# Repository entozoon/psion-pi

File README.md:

# Psion Pi

Personal electronics project; Attempting to build a modern PDA clamshell computer in a likeness of the venerable Psion 5mx.

4 years into this project, some significant changes, namely wide screen, LG Phenom keyboard and Pi 4 (significantly more capable.. the previous Zero/Zero 2/3 all put me off)

<!---KANBAN
# To Do
- Battery build protected/stepped-up/hooked up
- Battery level (physical or reported to Pi, ie. via lipo fuel gauge)
- Case build
- Keyboard scanning/emulation
- Wireless charging if possible

# In Progress
- Power converters

# Done
- Bootable Pi
- LCD screen
- Touch screen
- Figure power requirements
KANBAN--->

## Aims

- Tasty colour screen - For enjoyable video playback
- Quality keyboard - So it's legitimately useful
- Portability - I'm under no illusions that it'll be larger than a Psion 5mx/Jornada (as would be ideal) because of screen size and battery demands but if it's smaller than a Netbook Pro I'll be happy
- Sturdiness - Every single bit will be inherently fragile as heck, so I need to 3D print the structure real good

## Ingredients

- Battery pack (18650 3S parallel 3.7v) - Home-made li-ion for the win!
- Charging circuity and steps ups with protection - So I don't blow myself up
- Raspberry Pi
- LG Phenom keyboard, or maybe Psion Netbook (previously Psion 5mx, prepreviously Dell Foldable) - What? No way! Yes way. **Yes frickin way**
- Keyboard USB interface - Arduino or ESP8266, hand-built
- 7.9" Capacitive Touchscreen LCD 1024\*600 (Waveshare C Rev2.1)
- Mad efficient 1337 OS and warez, legit IDE, etc - We'll start with vanilla Raspbian first though

## "Wait, so what's this repo even for then?"

Notes about how I set everything up for reference, config files, microcontroller code for keyboard interface, etc etc.

## Setting up the Pi

Raspbian Stretch (2017-08-16) did **not** work, no matter what (with Pi Zeroes).

Raspbian Jessie (2017-07-05) did though, but more recently..

Raspberry Pi OS Bullseye [(2021-11-08)](https://downloads.raspberrypi.org/raspios_lite_arm64/images/) is 64-bit(!)

Installed on a 16gb microSD with win32diskImager (or similar) then, _before removing_, (in the windows partition, or `/boot` on unix):

1. Create a blank file called `ssh` on it, e.g.

```bash
cd /d h:
echo > ssh
```

2. Create `wpa_supplicant.conf` containing:

```bash
country=US
ctrl_interface=DIR=/var/run/wpa_supplicant GROUP=netdev
update_config=1

network={
 ssid="NetworkName"
 scan_ssid=1
 psk="yourpassword"
 key_mgmt=WPA-PSK
}
```

3. Safely eject (they can become corrupt, trust)
4. Pop it in the Pi with HDMI and a keyboard; let it do its thing.

Any screen problems and it should still be SSH-able.

## LCD Screen - 7.9" Waveshare Widescreen 400×1280

### Enable HDMI current and whatnot

```bash
sudo nano /boot/config.txt
```

```bash
# Add support for 7.9" Waveshare LCD
# set current over USB to 1.2A
max_usb_current=1
hdmi_group=2
hdmi_mode=87
hdmi_timings=400 0 100 10 140 1280 10 20 20 2 0 0 0 60 0 43000000 3
# 1: 90°; 2: 180°C; 3: 270° (might not work, see next section)
#lcd_rotate=3
#hdmi_enable_4kp60=1
```

### Disable compositor

```bash
sudo raspi-config
```

6 Advanced menu then A3 and set Compositor to disabled.

### Rotate

Set orientation (right) in raspbian `preferences > screen configuration`.
This appears to have a bug where the settings don't persist after boot - it creates a file called dispsetup.sh but doesn't appear to run after login, at least on my current distro, so let's force it:

```bash
sudo nano /etc/xdg/lxsession/LXDE-pi/autostart
```

Append:

```
@/usr/share/dispsetup.sh
```

## Touch Setup

Automatic and orientated by long-pressing the 'rotate touch' button on the screen.

## Brightness

Powers happily from the touch USB input!!

Has 5 Settings, long press on/off on screen:

- 1 0.15A
- 2 0.16A
- 3 0.17A
- 4 0.19A
- 5 0.2A

## Fan Shim

```bash
git clone https://github.com/pimoroni/fanshim-python
cd fanshim-python
sudo ./install.sh
cd examples
sudo ./install-service.sh --on-threshold 65 --off-threshold 55 --delay 2
```

## Overclock

Make sure to use the fan shim!

```bash
sudo nano /boot/config.txt
```

```
# Overclock (all values typically unset, defaulting to 700mhz)
over_voltage=4
arm_freq=2000
```

More steps involved.. https://www.tomshardware.com/how-to/raspberry-pi-4-23-ghz-overclock

## Other settings

Disable dimming, etc.. https://www.waveshare.com/wiki/7.9inch_HDMI_LCD

## Power Usage

|                 Component | Usage (Amps +/- 0.05) |
| ------------------------: | --------------------- |
|                 Pi Zero W | 0.15 (unused)         |
|                      Pi 3 | 0.3 (idling)          |
|               Pi Zero 2 W | 0.3                   |
| Pi Zero 2 W (Overclocked) | 0.45                  |
|                           |                       |
|                      Pi 4 | 0.55 (idling)         |
|               7.9" Screen | 0.65                  |
|                           |                       |
|                     Total | 1.2                   |

Battery life estimates, according to my **[Super Useful Tool](https://battery-life.netlify.com/)**:

18650 x 1 (2500mah) = ~1h

18650 x 3 (7500mah) = ~3h

Mine are 20A maximum discharge.
If they're in parallel, you get more mAh and current capability, as it's shared around.
And anyway, 20A discharge? Fokk man, it'll be nowhere near. I just need a nice chonky boost module.
If it doesn't work, build a series one with 15A BMS etc.

## Keyboard

I got reasonably far in this repo with keyboard emulation on the Pi itself but.. I don't love it, and since then I reckon I've nailed [keyboard matrix scanning](https://github.com/entozoon/print-me-beech/blob/master/print-me-beech/src/keyboard.h) so I plan to pick a microcotroller with suitably choppy USB capabilities (32u4/STM32/Tiny?) to capture the input and emulate a USB keyboard. Much cleaner!

## OBSOLETE: Previous foldable keyboard

Dell Axim X5 Foldable Keyboard - what a hero of a warlock of a battlemage of a keyboard!
Disassembling it revealed it only has three IO:

- 3.3V in
- GND
- Data out

  Hooking that all up to a USB FTDI (data => RX), reveals some useful output with the following settings (e.g. in RealTerm):
  Port -> Baud: 4800,
  Display -> Display As: Hex

### Keymap

This wonderous diagram is courtesy of [Gavin Whelan](https://ambientmemory.com/), along with generally pointing me in the [right direction](https://ambientmemory.com/2017/02/20/dell-axim-x5-reverse-engineering/) to capture input.

    |------||------||------||------||------||------||------||------||------||------||------||-----||-----||--------|
    |  `~  ||  1!  ||  2@  ||  3#  ||  4$  ||  5%  ||  6^  ||  7&  ||  8*  ||  9(  ||  0)  || -_  ||  =+ ||  <-    |
    | 0ef1 || 16e9 || 1ee1 || 26d9 || 25da || 2ed1 || 36c9 || 3dc2 || 3ec1 || 46b9 || 45ba || 4e  ||  55 || 718e   |
    |      ||      ||      ||      ||      ||      ||      ||      ||      ||      ||      || b1  ||  aa ||        |
    |------||------||------||------||------||------||------||------||------||------||------||-----||-----||--------|
    |--------||------||------||------||------||------||------||------||------||------||------||-----||-----||------|
    |  ->|   ||  Q   ||  W   ||  E   ||  R   ||  T   ||  Y   ||  U   ||  I   ||  O   ||  P   || {   || }   ||  |\  |
    | 0df2   || 15ea || 1de2 || 24db || 2dd2 || 2cd3 || 35ca || 3cc3 || 43bc || 44bb || 4db2 || 54ab|| 5ba4|| 5da2 |
    |        ||      ||      ||      ||      ||      ||      ||      ||      ||      ||      || [   || ]   ||      |
    |--------||------||------||------||------||------||------||------||------||------||------||-----||-----||------|
    |----------||------||------||------||------||------||------||------||------||------||------||------||----------|
    |  caps    ||  A   ||  S   ||  D   ||  F   ||  G   ||  H   ||  J   ||  K   ||  L   ||  ;:  ||  '"  ||  enter   |
    | 58a7     || 1ce3 || 1be4 || 23dc || 2bd4 || 34cb || 33cc || 3bc4 || 42bd || 4bb4 || 4cb3 || 52ad || 5aa5     |
    |          ||      ||      ||      ||      ||      ||      ||      ||      ||      ||      ||      ||          |
    |----------||------||------||------||------||------||------||------||------||------||------||------||----------|
    |--------------||------||------||------||------||------||------||------||------||------||------||------||------|
    |  shift       ||  Z   ||  X   ||  C   ||  V   ||  B   ||  N   ||  M   ||  ,<  ||  .>  ||  /?  ||  ^   ||  rsh |
    | 12ed         || 1ae5 || 22dd || 21de || 2ad5 || 32cd || 31ce || 3ac5 || 41be || 49b6 || 4ab5 || 28d7 || 59a6 |
    |              ||      ||      ||      ||      ||      ||      ||      ||      ||      ||      ||  |   ||      |
    |--------------||------||------||------||------||------||------||------||------||------||------||------||------|
    |------||------||------||------||------------------------------||------||------||------||------||------||------|
    |  fn  || ctrl ||  win ||  ie  ||           space              || alt  || ctrl ||  del || <--  ||  |   ||  --> |
    | 02fd || 14eb || 07f8 || 708f ||           5ca3               || 11ee || 738c || 6699 || 5ea1 || 609f || 2fd0 |
    |      ||      ||      ||      ||                              ||      ||      ||      ||      ||  v   ||      |
    |------||------||------||------||------------------------------||------||------||------||------||------||------|

## OBSOLETE: Previous LCD screen attempts

### 7.9" on Pi Zero 2

GRAPHICS?
Apparently an advanced graphics thing? Needs experimentation though:

```bash
sudo nano /usr/share/X11/xorg.conf.d/99-fbturbo.conf
```

Comment out the line, a la:

```
#       Driver          "fbturbo"
```

TOUCH?

```bash
sudo apt-get install xserver-xorg-input-libinput
sudo mkdir /etc/X11/xorg.conf.d
sudo cp /usr/share/X11/xorg.conf.d/40-libinput.conf /etc/X11/xorg.conf.d/
sudo nano /etc/X11/xorg.conf.d/40-libinput.conf
```

Find the touchscreen section and add _one of_ the following lines, a la:

```bash
Section "InputClass"
        Identifier "libinput touchscreen catchall"
        MatchIsTouchscreen "on"
        # Option "CalibrationMatrix" "0 1 0 -1 0 1 0 0 1" # mykemod
        # Option "CalibrationMatrix" "0 1 0 -1 0 1 0 0 1" # mykemod 90 deg
        # Option "CalibrationMatrix" "-1 0 1 0 -1 1 0 0 1" # mykemod 180 deg
        Option "CalibrationMatrix" "0 -1 1 1 0 0 0 0 1" # mykemod 270 deg
        MatchDevicePath "/dev/input/event*"
        Driver "libinput"
EndSection
```

### 7" Waveshare

Either copy the `config.txt` in this repo, or bosh this stuff into yours (in windows partition or `/boot` on unix):

```bash
# Add support for Waveshare 7" capacitive Touch (C) v2.1
# set current over USB to 1.2A
max_usb_current=1

# overscan to adjust image position
overscan_left=0
overscan_right=0
overscan_top=0
overscan_bottom=0

# HDMI config
hdmi_drive=1
hdmi_ignore_edid=0xa5000080
hdmi_group=2
hdmi_mode=87

# 1024x600 display
hdmi_cvt=1024 600 60 6 0 0 0
```

### 5" model A screen

Elegoo, a cheaper version of Wavershare model A (not B)

```bash
cd ~
wget https://github.com/entozoon/psion-pi/raw/master/lib/LCD-show-170703.tar.gz
tar xzvf *.tar.gz
rm *.tar.gz
cd LCD-show/
chmod +x LCD5-show
./LCD5-show
```

### 3.5"

Raspbian Stretch (2017-11-29)

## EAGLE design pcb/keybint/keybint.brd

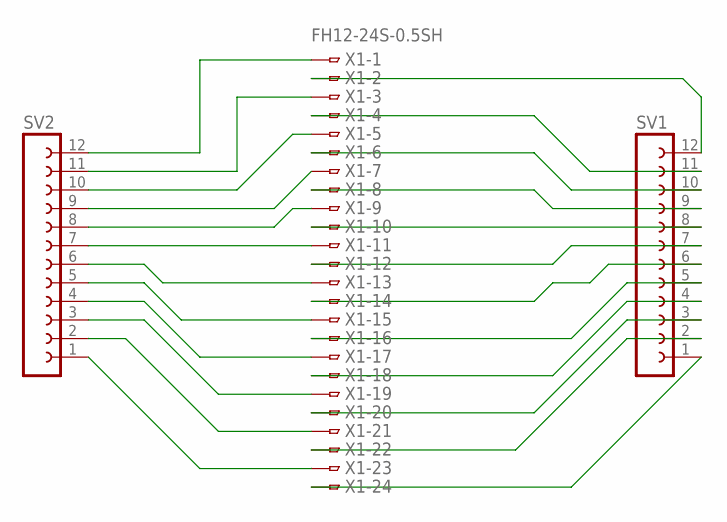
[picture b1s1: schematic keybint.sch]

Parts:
SV1, SV2: FE12-1; FE12
X1: FH12-24S-0.5SH

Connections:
unnamed: SV2.12, X1.1
unnamed: SV1.12, X1.2
unnamed: SV2.11, X1.3
unnamed: SV1.11, X1.4
unnamed: SV2.10, X1.5
unnamed: SV1.10, X1.6
unnamed: SV2.9, X1.7
unnamed: SV1.9, X1.8
unnamed: SV2.8, X1.9
unnamed: SV1.8, X1.10
unnamed: SV2.7, X1.11
unnamed: SV1.7, X1.12
unnamed: SV2.6, X1.13
unnamed: SV1.6, X1.14
unnamed: SV2.5, X1.15
unnamed: SV1.5, X1.16
unnamed: SV2.4, X1.17
unnamed: SV1.4, X1.18
unnamed: SV2.3, X1.19
unnamed: SV1.3, X1.20
unnamed: SV2.2, X1.21
unnamed: SV1.2, X1.22
unnamed: SV2.1, X1.23
unnamed: SV1.1, X1.24

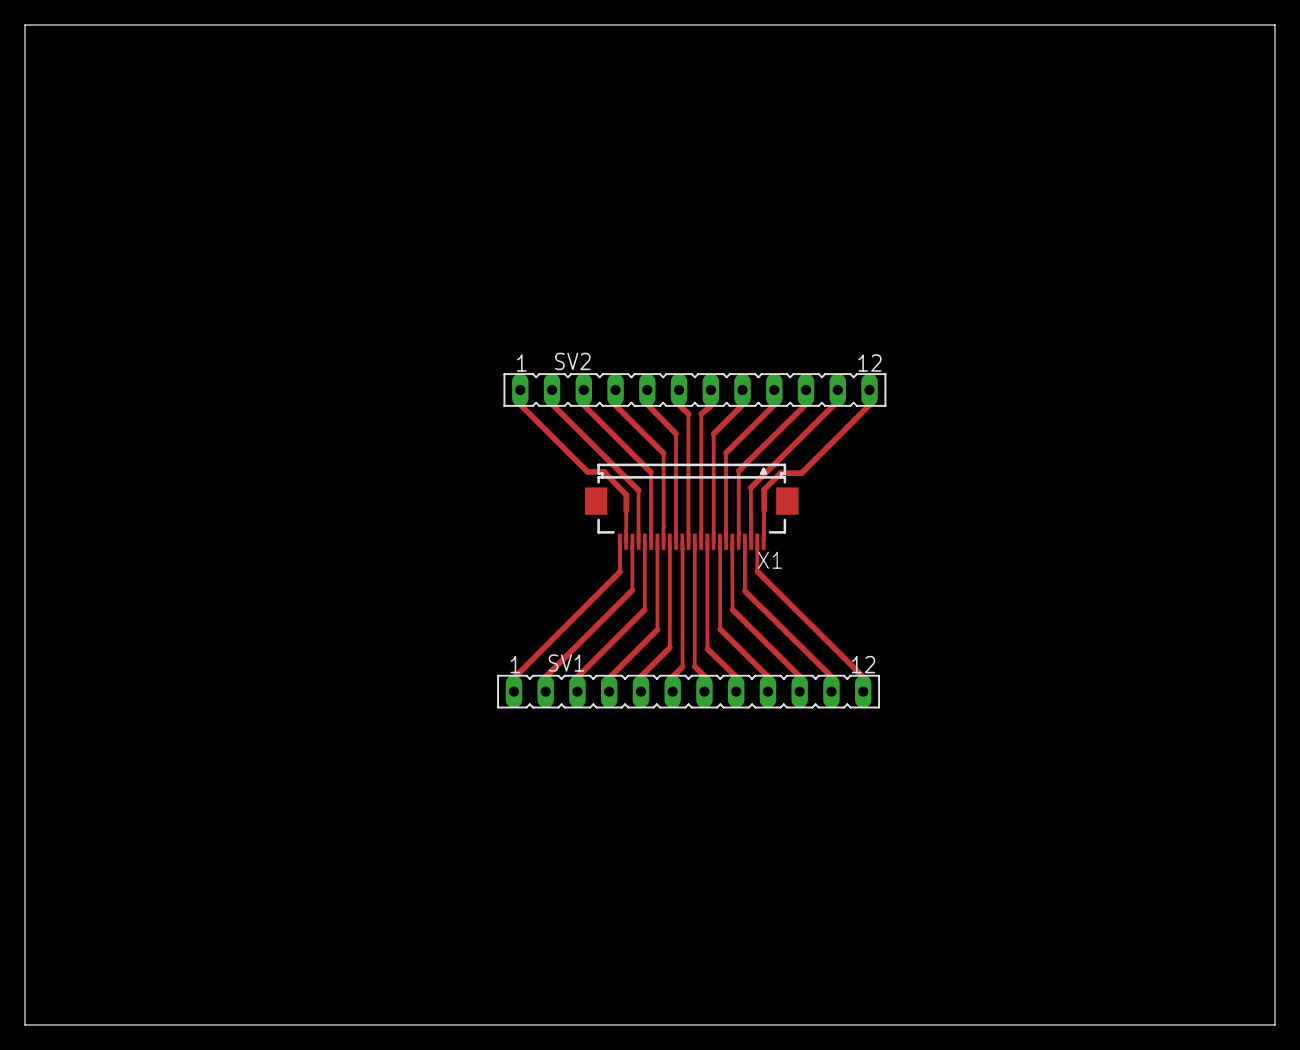
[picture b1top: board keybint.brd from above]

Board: 2 copper layers, 100.0 x 80.0 mm, 3 parts (0 on the bottom side), 24 nets.

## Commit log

2017-08-31 Humble beginnings
2017-08-31 Pi setup and 7" LCD instructions (fingers crossed!)
2017-08-31 Knolling
2017-08-31 Kanban update
2017-08-31 Aspect ratio tweak
2017-09-03 Thinking about power, hash tag yikes
2017-09-03 Flickery tbh
2017-09-04 Battery stats
2017-09-04 Updating kanban (and kanban generator itself)
2017-09-10 Tinkering
2017-09-10 LCD touch library
2017-09-10 Added 5" resistive touch notes
2017-09-20 Finally figured how to export .ai to .svg for fritzing import
2017-09-20 Nothing really yet
2018-02-22 Getting somewhere with serial keyboard emulation and interface
2019-04-23 Config update
2021-11-10 4 years later!
2021-11-11 Ergh
2021-11-20 Updating notes
2021-11-20 I'll never be happy with my keyboard choice..
2021-11-20 Also never happy with computer choice either
2021-11-20 A little formatting while I'm here
